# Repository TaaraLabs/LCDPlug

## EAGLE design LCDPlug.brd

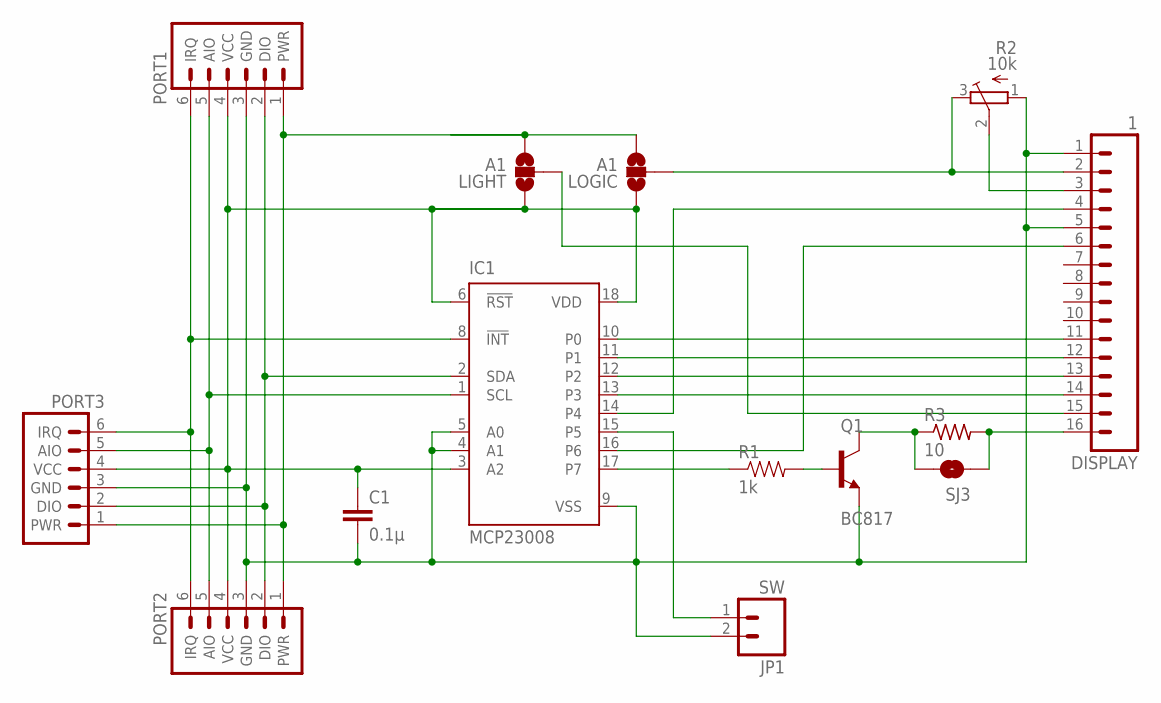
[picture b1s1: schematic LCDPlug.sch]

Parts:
C1: 0.1µ; 0603-CAP
DISPLAY: 1; 1X16
IC1: MCP23008; SO18W
JP1: SW; 1X02
LIGHT: A1; SJ_2
LOGIC: A1; SJ_2
PORT1, PORT2, PORT3: JEEPORT; PORT6PIN
Q1: BC817; SOT23-3
R1: 1k; 0603-RES
R2: 10k; SM-42/43W
R3: 10; 0204/7
SJ3: SOLDERJUMPERNO; SJ_2S-NO

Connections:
GND: C1.2, DISPLAY.1, DISPLAY.5, IC1.4 (A1), IC1.5 (A0), IC1.9 (VSS), JP1.2, PORT1.3 (GND), PORT2.3 (GND), PORT3.3 (GND), Q1.2 (E), R2.1 (A)
unnamed: IC1.8 (!INT), PORT1.6 (IRQ), PORT2.6 (IRQ), PORT3.6 (IRQ)
unnamed: IC1.1 (SCL), PORT1.5 (AIO), PORT2.5 (AIO), PORT3.5 (AIO)
unnamed: DISPLAY.11, IC1.10 (P0)
unnamed: DISPLAY.12, IC1.11 (P1)
unnamed: IC1.2 (SDA), PORT1.2 (DIO), PORT2.2 (DIO), PORT3.2 (DIO)
unnamed: DISPLAY.13, IC1.12 (P2)
unnamed: DISPLAY.14, IC1.13 (P3)
unnamed: DISPLAY.15, LIGHT.2
unnamed: Q1.3 (C), R3.1, SJ3.2
unnamed: IC1.17 (P7), R1.1
unnamed: Q1.1 (B), R1.2
unnamed: DISPLAY.6, IC1.16 (P6)
unnamed: IC1.15 (P5), JP1.1
unnamed: DISPLAY.4, IC1.14 (P4)
unnamed: DISPLAY.2, LOGIC.2, R2.3 (E)
unnamed: DISPLAY.16, R3.2, SJ3.1
unnamed: DISPLAY.3, R2.2 (S)
PWR: LIGHT.3, LOGIC.3, PORT1.1 (PWR), PORT2.1 (PWR), PORT3.1 (PWR)
VCC: C1.1, IC1.3 (A2), IC1.6 (!RST), IC1.18 (VDD), LIGHT.1, LOGIC.1, PORT1.4 (VCC), PORT2.4 (VCC), PORT3.4 (VCC)

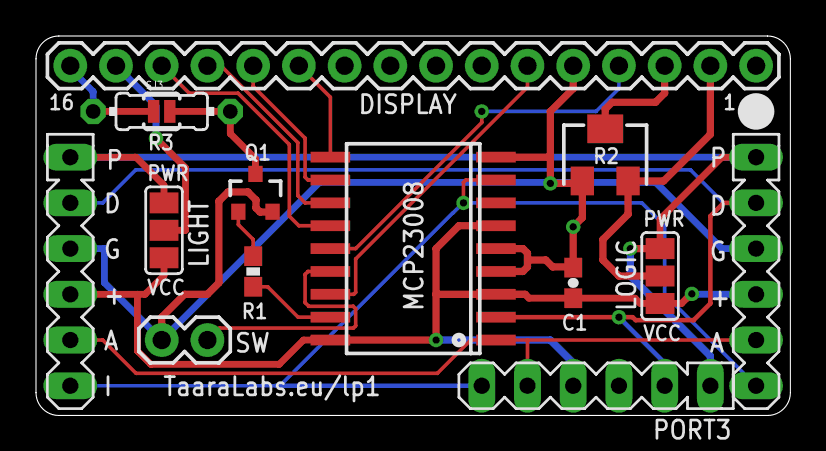
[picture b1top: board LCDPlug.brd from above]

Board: 2 copper layers, 41.9 x 21.1 mm, 14 parts (0 on the bottom side), 20 nets.

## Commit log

2015-02-01 :boom::camel: Added .gitattributes & .gitignore files
2015-02-01 LCDPlug
